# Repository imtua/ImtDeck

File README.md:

# ImtDeck - Your own Cyberdeck

ImtDeck, a cyberdeck designed by **Imtiaz Ahmed**. In ImtDeck, basic tasks and a light AI can be run easily. In this project, it technically contains 2 projects, **ImtDeck-Carrier** and **ImtKeeb-Ortho62**.

**Stardance** project: https://stardance.hackclub.com/projects/54966

# Wanted Ingredients to craft ImtDeck
## Main items-
- **Lattepanda MU + Carrier + Active Cooler** - $250.00 - 1
- **11.6 Inch Screen** - $129.00 - 1
- **Antenna** - $7.99 - 1
- **Audio Card from Waveshare** - $51.71 - 1
- **KAILH Linear Low Profile Switches** - $56.82 - 3
- **Chosfox CFX BoW Keycap Set** - $33.00 - 1
- **TPS43-201A-S** - $13.87 - 1
- **Power Bank** - $13.00 - 1
- **WIFI Card** - $28.00 - 1
- **Pi Pico** - $12.00 - 1
- **USB Micro Cord** - $13.00 - 1
- **40MM Speaker** - $6.00 - 1
- **Tiny SSD** - $70.00 - 1

Check <a href="https://github.com/imtua/ImtDeck/blob/main/ImtDeck%20BOM.csv"><b>ImtDeck BOM.csv</b></a> for links.

## Hardwares-
- 4x M4 Threaded heat-set brass inserts
- 26x M3 Threaded heat-set brass inserts
- 6x M3x8mm Tapered head bolts
- 8x M3x12mm Tapered head bolts
- 4x M3x8mm Socket head bolts
- 4x M3x10mm Socket head bolts
- 2x M4x14mm Socket head bolts
- 2x M4x16mm Socket head bolts
- 2x M4x24mm Socket head bolts
- 1x 7mm OD Carbon fiber rod, 310mm long (can be any material)
- 2x 6.5x2.5mm neodymium magnets (optional)
- 1x Cabinet handle with 4-inch spacing between ends (optional)

# ImtKeeb-Ortho62 - Designed Keyboard for ImtDeck
**ImtKeeb-Ortho62** is a low-profile ortholinear 62 key keyboard that contains a trackpad in it.

**PCB of ImtKeeb-Ortho62:**

**3D PCB of ImtKeeb-Ortho62:**

**ImtKeeb-Ortho62 will feature-**
- <a href="https://www.amazon.com/dp/B0B3MN1ZLW"><b>KAILH Low Profile Switch 1350 Chocolate</b></a> - 62 Switches.
- <a href="https://chosfox.com/collections/keycaps/products/chocfox-bow"><b>Chosfox CFX BoW Keycap Set</b></a> - 62 Keycaps.
- <a href="https://www.digikey.com/en/products/detail/azoteq-pty-ltd/TPS43-201A-S/7164940"><b>TPS43-201A-S</b></a> Trackpad.
- <a href="https://store.roboticsbd.com/raspberry-pi/1599-raspberry-pi-pico-robotics-bangladesh.html"><b>Raspberry Pi Pico</b></a> - Brain of the ImtKeeb-Ortho62.

**Files of ImtKeeb-Ortho62**
- <a href="https://github.com/imtua/ImtDeck/blob/main/production/ImtKeeb-Ortho62/ImtKeeb-Ortho62%20Gerber.zip"><b>ImtKeeb-Ortho62 Gerber Files</a></b> - **/Production/ImtKeeb-Ortho62/ImtKeeb-Ortho62 Gerber.zip**
- <a href="https://github.com/imtua/ImtDeck/blob/main/PCB/ImtKeeb-Ortho62/ImtKeed-Ortho62.kicad_sch"><b>ImtKeeb-Ortho62 Schematics</a><b> - **/PCB/ImtKeeb-Ortho62/ImtKeed-Ortho62.kicad_sch**
- <a href="https://github.com/imtua/ImtDeck/blob/main/PCB/ImtKeeb-Ortho62/ImtKeeb-Ortho62.kicad_pcb"><b>ImtKeeb-Ortho62 PCB</a></b> - **/PCB/ImtKeeb-Ortho62/ImtKeed-Ortho62.kicad_pcb**
- <a href="https://github.com/imtua/ImtDeck/tree/main/QMK"><b>Keyboard QMK config files</b></a> - /QMK

This can be used without the ImtDeck.

# ImtDeck-Carrier - Carrier for MU LattePanda
**ImtDeck-Carrier** is a carrier that holds the lattepanda and makes it route and connect to devices like the monitor, fan, keyboard etc.

**Schematic of ImtDeck-Carrier:**

**PCB of ImtDeck-Carrier:**

**ImtDeck-Carrier** will hold the Lattepanda MU in its place and will distribute powers between items. 

**Files of ImtKeeb-Ortho62**
- <a href="https://github.com/imtua/ImtDeck/blob/main/production/ImtDeck-Carrier/ImtDeck-Carrier%20Gerber.zip"><b>ImtDeck-Carrier Gerber Files</a></b> - **/Production/ImtDeck-Carrier/ImtDeck-Carrier Gerber.zip**
- <a href="https://github.com/imtua/ImtDeck/blob/main/PCB/ImtDeck-Carrier/ImtDeck-Carrier.kicad_sch"><b>ImtDeck-Carrier Schematics</a><b> - **/PCB/ImtDeck-Carrier/ImtDeck-Carrier.kicad_sch**
- <a href="https://github.com/imtua/ImtDeck/blob/main/PCB/ImtDeck-Carrier/ImtDeck-Carrier.kicad_pcbb"><b>ImtDeck-Carrier PCB</a></b> - **/PCB/ImtDeck-Carrier/ImtDeck-Carrier.kicad_pcb**

# Features
- ImtDeck will feature Linux Mint OS in it.
- With it, you can access different tools and a lightweight offline AI in it.
- All ready-to-go device.
- Can play low-end games on it.
- Features Keyboard and Trackpad.
- Sound System.
- Can run everything a normal laptop can.

# Conclusion

Made by <a href="https://github.com/imtua"><b>Imtiaz</b></a> with the help of <a href="https://hackclub.com"><b>Hack Club</a></b>

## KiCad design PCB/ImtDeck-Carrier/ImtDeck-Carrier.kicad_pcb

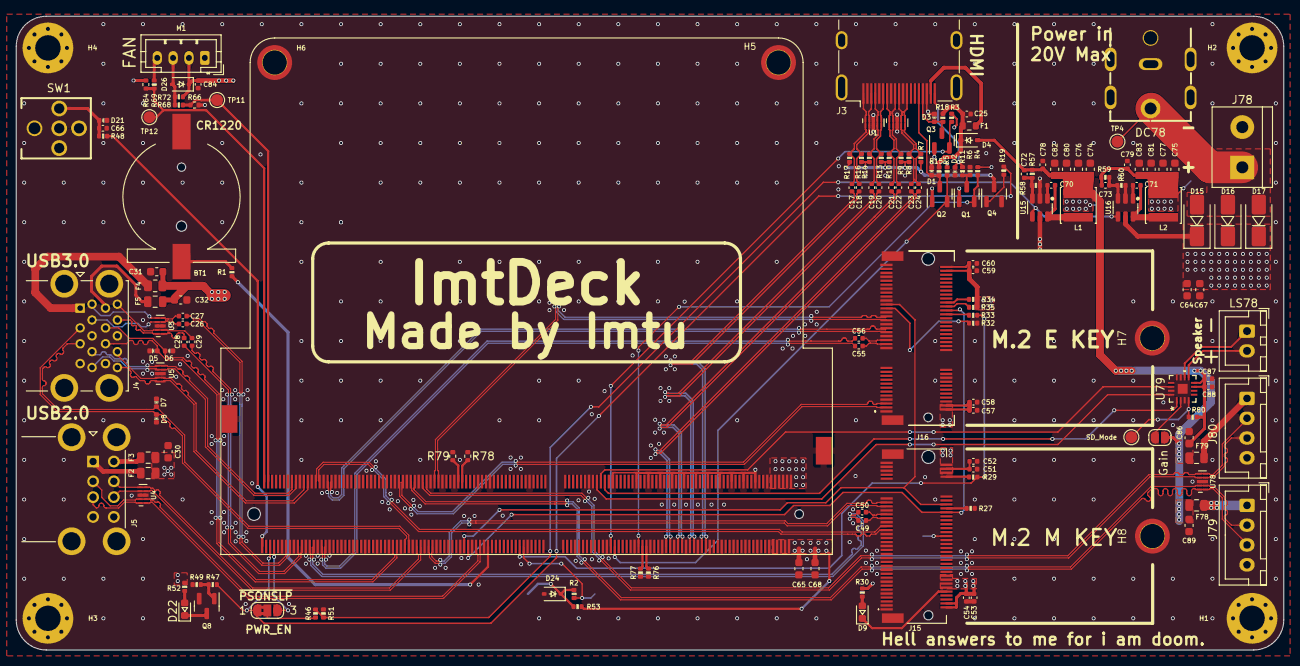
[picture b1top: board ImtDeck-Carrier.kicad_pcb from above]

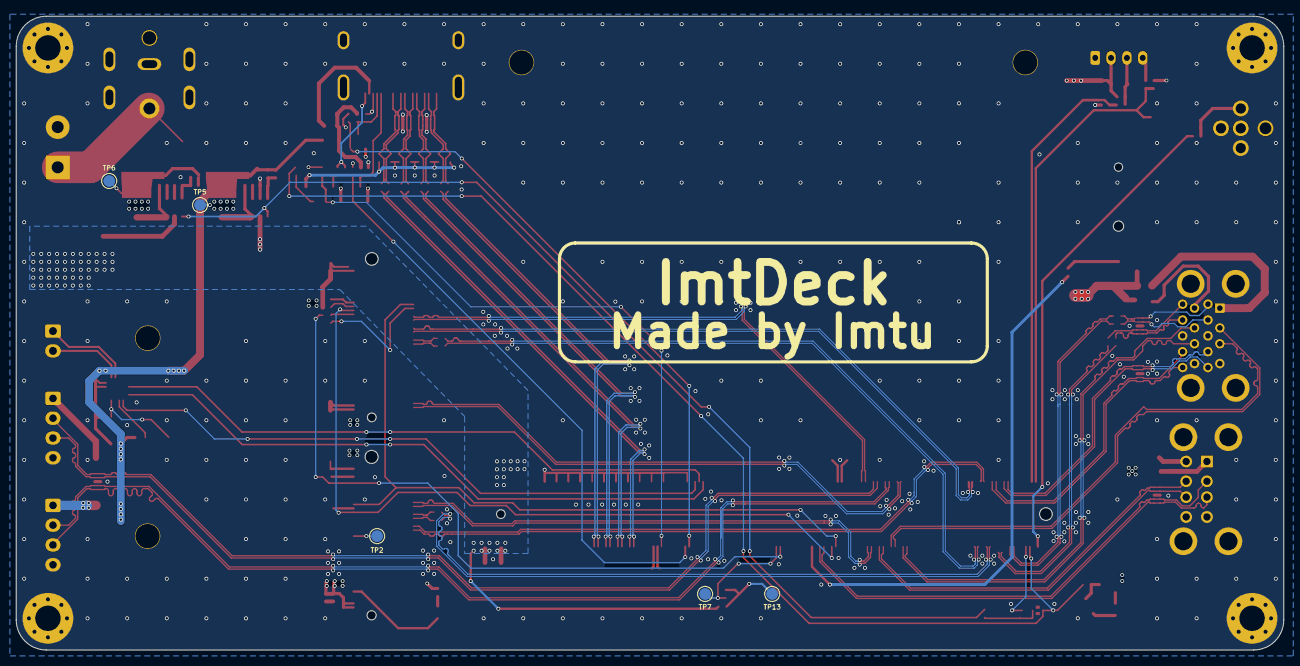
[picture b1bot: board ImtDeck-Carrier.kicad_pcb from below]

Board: 4 copper layers, 160.0 x 80.0 mm, 170 parts (5 on the bottom side), 126 nets.

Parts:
A1: LattePanda_Mu; LattePanda_Module_H8.0mm_Horizontal
BT1: Battery_Cell; Battery_Holder_CR1220_S8411-45R
C17, C18, C19, C20, C21, C22, C23, C24, C25, C26, C27, C28, C29, C52, C54, C58, C60, C70, C71, C78, C79, C84: 100nF/50V; C_0402_1005Metric
C30, C31, C32, C64, C65, C67, C68, C74, C75, C76, C77, C80, C81, C82, C83, C86, C89: 22uF/10V; C_0603_1608Metric
C49, C50, C55, C56: 220nF/50V; C_0402_1005Metric
C51, C53, C57, C59: 10uF/10V; C_0402_1005Metric
C66: 1uF/16V; C_0402_1005Metric
C72, C73: 12pF/50V; C_0402_1005Metric
C87: 10uF; C_0402_1005Metric
C88: 100nF; C_0402_1005Metric
D1, D2, D3, D5, D6, D7, D8, D21: ESD5V0B03; D_0402_1005Metric
D4, D26: 1N5819WS; D_SOD-323
D9, D22: LED_G; LED_0603_1608Metric
D15, D16, D17: SS54; D_SMA
D24: 3V3 Izt=5mA; D_SOD-323
DC78: DC-042C-W-2.0; DC-IN-TH_DC-042C-W-2.0
F1: 6V/50mA; R_0603_1608Metric
F2, F3, F78, F79: 6V/1A; Fuse_0805_2012Metric
F4: 6V/2A; R_0805_2012Metric
F5: 6V/2A; Fuse_0805_2012Metric
Gain: SolderJumper_2_Open; SolderJumper-2_P1.3mm_Open_RoundedPad1.0x1.5mm
H1, H2, H3, H4: MountingHole_Pad; MountingHole_3.2mm_M3_Pad_Via
H5, H6: MountingHole_Pad; MountingHole_3mm_M2_Pad_TopOnly
H7, H8: MountingHole_M2.0; MountingHole_3mm_M2_Pad_TopOnly
J3: HDMI_A; HDMI_A_Molex_208658-1001_Horizontal
J4: USB3_A_Stacked; USB3_A_Molex_48406-0001_Horizontal_Stacked
J5: USB_A_Stacked; USB_A_CUI_UJ2-ADH-TH_Horizontal_Stacked
J15: Bus_M.2_Socket_M; PCIe_M.2_Connectors_P=0.5mm_H=4.2mm_KeyM
J16: Bus_M.2_Socket_E; PCIe_M.2_Connectors_P=0.5mm_H=4.2mm_KeyE
J78: Screw_Terminal_01x02; TerminalBlock_bornier-2_P5.08mm
J79, J80: Conn_01x04_Socket; JST_XH_B4B-XH-A_1x04_P2.50mm_Vertical
JP79: SolderJumper_3_Open; SolderJumper-3_P1.3mm_Bridged2Bar12_RoundedPad1.0x1.5mm_Num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
L1, L2: 2.2uH/4.3A; L_Sunlord_SWPA4020S
LS78: Speaker; JST_XH_B2B-XH-A_1x02_P2.50mm_Vertical
M1: Fan_4pin; JST_PH_B4B-PH-K_1x04_P2.00mm_Vertical
Q1, Q8: 2N7002; SOT-23
Q2, Q3, Q4: 2SK3018; SOT-23
R1, R11, R47: 1K/1%; R_0402_1005Metric
R2, R34, R35, R49, R58, R78, R79: 10K/1%; R_0402_1005Metric
R3, R5, R15, R18, R19, R30, R52, R53: 2.2K/1%; R_0402_1005Metric
R4: 1M/1%; R_0402_1005Metric
R6, R59, R66, R68: 21.5K/1%; R_0402_1005Metric
R7, R8, R9, R10, R13, R14, R16, R17: 470R/1%; R_0402_1005Metric
R27, R29, R32, R33: 0R/1%; R_0402_1005Metric
R46, R48, R69: 100R/1%; R_0402_1005Metric
R51, R76, R77: 100K/1%; R_0402_1005Metric
R57: 75K/1%; R_0402_1005Metric
R60, R64, R72: 4.7K/1%; R_0402_1005Metric
R80: 1M; R_0402_1005Metric
SD_Mode: TestPoint; TestPoint_Pad_D1.5mm
SW1: SW_Push; SW-TH_TM-007-D1-A-03
TP2, TP4, TP5, TP6, TP7, TP11, TP12, TP13: TestPoint; TestPoint_Pad_D1.5mm
U1, U2: TPAZ1023-04F; Diodes_UDFN-10_1.0x2.5mm_P0.5mm
U3, U4, U5, U78: ULC0524P; Diodes_UDFN-10_1.0x2.5mm_P0.5mm
U15, U16: SY8253ADC; TSOT-23-6
U79: MAX98357AETE+T; 21-0136I_T1633-4_MXM

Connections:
5V_HDMI_VCC: C25.1, D4.1 (K), F1.1, R15.1, R18.1
+3V3: C51.2, C52.2, C53.2, C54.2, C57.2, C58.2, C59.2, C60.2, C73.1, C75.2, C77.2, C79.1, C81.2, C83.2, J15.2 (3.3V), J15.4 (3.3V), J15.12 (3.3V), J15.14 (3.3V), J15.16 (3.3V), J15.18 (3.3V), J15.70 (3.3V), J15.72 (3.3V), J15.74 (3.3V), J16.2 (3.3V), J16.4 (3.3V), J16.72 (3.3V), J16.74 (3.3V), L2.2, Q1.1 (G), Q2.1 (G), Q3.1 (G), R3.1, R4.1, R5.1, R30.2, R34.2, R35.1, R52.2, R59.2, R64.1, TP6.1
+5V: C30.2, C31.2, C32.2, C72.1, C74.2, C76.2, C78.1, C80.2, C82.2, C84.1, C86.2, C87.1, C88.1, C89.2, D4.2 (A), D26.1 (K), F2.1, F3.1, F4.1, F5.1, F78.1, F79.1, Gain.1 (A), L1.2, M1.2 (+), R57.2, R72.1, R80.1, TP5.1, U79.7 (VDD), U79.8 (VDD)
+12V: D15.2 (A), D16.2 (A), D17.2 (A), DC78.4, J78.1, TP4.1
+BATT: A1.115 (VBAT), R1.1
/Fan_Temp/FAN_1_PWM: A1.2 (FAN1_PWM), R64.2, R69.1, TP12.1
/Fan_Temp/FAN_1_TAC: A1.4 (FAN1_TAC), R66.1, R68.2, TP11.1
/HDMI/DDC_SCL: D1.2 (A2), J3.15 (SCL), Q2.3 (D), R15.2
/HDMI/DDC_SDA: D3.2 (A2), J3.16 (SDA), Q3.3 (D), R18.2
/HDMI/DDI_B_DDC_SCL: A1.171 (DDIB_DDC_SCL), Q2.2 (S), R5.2
/HDMI/DDI_B_DDC_SDA: A1.169 (DDIB_DDC_SDA), Q3.2 (S), R3.2
/HDMI/DDI_B_HPD: A1.183 (DDIB_HPD), Q1.2 (S), R4.2
/HDMI/DDI_B_TX0+: A1.217 (DDIB_TX0+), C17.1
/HDMI/DDI_B_TX0-: A1.215 (DDIB_TX0-), C18.1
/HDMI/DDI_B_TX1+: A1.211 (DDIB_TX1+), C19.1
/HDMI/DDI_B_TX1-: A1.209 (DDIB_TX1-), C20.1
/HDMI/DDI_B_TX2+: A1.205 (DDIB_TX2+), C21.1
/HDMI/DDI_B_TX2-: A1.203 (DDIB_TX2-), C22.1
/HDMI/DDI_B_TX3+: A1.199 (DDIB_TX3+), C23.1
/HDMI/DDI_B_TX3-: A1.197 (DDIB_TX3-), C24.1
/HDMI/HPD: D2.2 (A2), J3.19 (HPD), R11.2
/HDMI/TMDS_CK+: C23.2, J3.10 (CK+), R8.1, U2.4, U2.7 (NC)
/HDMI/TMDS_CK-: C24.2, J3.12 (CK-), R7.1, U2.5, U2.6 (NC)
/HDMI/TMDS_D0+: C21.2, J3.7 (D0+), R10.1, U2.1, U2.10 (NC)
/HDMI/TMDS_D0-: C22.2, J3.9 (D0-), R9.1, U2.2, U2.9 (NC)
/HDMI/TMDS_D1+: C19.2, J3.4 (D1+), R14.1, U1.4, U1.7 (NC)
/HDMI/TMDS_D1-: C20.2, J3.6 (D1-), R13.1, U1.5, U1.6 (NC)
/HDMI/TMDS_D2+: C17.2, J3.1 (D2+), R17.1, U1.1, U1.10 (NC)
/HDMI/TMDS_D2-: C18.2, J3.3 (D2-), R16.1, U1.2, U1.9 (NC)
/LattePanda Module/HSIO_0_TX+: A1.13 (HSIO0_TX+), C27.1
/LattePanda Module/HSIO_0_TX-: A1.15 (HSIO0_TX-), C26.1
/LattePanda Module/HSIO_1_TX+: A1.19 (HSIO1_TX+), C29.1
/LattePanda Module/HSIO_1_TX-: A1.21 (HSIO1_TX-), C28.1
/LattePanda Module/HSIO_2_RX+: A1.28 (HSIO2_RX+), J15.43 (PERp0/SATA-B-)
/LattePanda Module/HSIO_2_RX-: A1.30 (HSIO2_RX-), J15.41 (PERn0/SATA-B+)
/LattePanda Module/HSIO_2_TX+: A1.25 (HSIO2_TX+), C49.1
/LattePanda Module/HSIO_2_TX-: A1.27 (HSIO2_TX-), C50.1
/LattePanda Module/HSIO_3_RX+: A1.34 (HSIO3_RX+), J16.41 (PERp0)
/LattePanda Module/HSIO_3_RX-: A1.36 (HSIO3_RX-), J16.43 (PERn0)
/LattePanda Module/HSIO_3_TX+: A1.31 (HSIO3_TX+), C55.1
/LattePanda Module/HSIO_3_TX-: A1.33 (HSIO3_TX-), C56.1
/LattePanda Module/REFCLK0+: A1.85 (REFCLK0+), J15.53 (REFCLKn)
/LattePanda Module/REFCLK0-: A1.87 (REFCLK0-), J15.55 (REFCLKp)
/LattePanda Module/REFCLK3+: A1.88 (REFCLK3+), J16.47 (REFCLKp0)
/LattePanda Module/REFCLK3-: A1.90 (REFCLK3-), J16.49 (REFCLKn0)
/LattePanda Module/SLS_S3: A1.7 (SLS_S3), JP79.3 (B)
/LattePanda Module/SUSCLK_WIFI: A1.131 (SUSCLK), R29.2, R33.2
/LattePanda Module/USB_2_P7+: A1.70 (USB2_P4+), J16.3 (USB_D+)
/LattePanda Module/USB_2_P7-: A1.72 (USB2_P4-), J16.5 (USB_D-)
/LattePanda Module/~PWR_SW: A1.1 (~PWRBTN), R48.2
/M.2 E&M Key/CON_PCIE_TX_0+: C55.2, J16.35 (PETp0)
/M.2 E&M Key/CON_PCIE_TX_0-: C56.2, J16.37 (PETn0)
/M.2 E&M Key/CON_PCIE_TX_1+: C49.2, J15.49 (PETp0/SATA-A+)
/M.2 E&M Key/CON_PCIE_TX_1-: C50.2, J15.47 (PETn0/SATA-A-)
/M.2 E&M Key/~CLKREQE: J16.53 (~CLKREQ0), R32.1
/M.2 E&M Key/~CLKREQM: J15.52 (~CLKREQ), R27.1
/PSU/PWR_EN: R46.2, R51.2, U15.4 (EN), U16.4 (EN)
/USB2.0&USB3.0/CON_USB1_D_N: A1.109 (USB2_P5-), J5.2 (D1-), U4.2, U4.9 (NC)
/USB2.0&USB3.0/CON_USB1_D_P: A1.111 (USB2_P5+), J5.3 (D1+), U4.1, U4.10 (NC)
/USB2.0&USB3.0/CON_USB2_D_N: A1.79 (USB2_P3-), J5.6 (D2-), U4.5, U4.6 (NC)
/USB2.0&USB3.0/CON_USB2_D_P: A1.81 (USB2_P3+), J5.7 (D2+), U4.4, U4.7 (NC)
/USB2.0&USB3.0/CON_USB3_D_N: A1.73 (USB2_P2-), D8.2 (A2), J4.2 (D1-)
/USB2.0&USB3.0/CON_USB3_D_P: A1.75 (USB2_P2+), D7.2 (A2), J4.3 (D1+)
/USB2.0&USB3.0/CON_USB3_SSRX_N: A1.18 (HSIO0_RX-), J4.5 (SSRX1-), U5.4, U5.7 (NC)
/USB2.0&USB3.0/CON_USB3_SSRX_P: A1.16 (HSIO0_RX+), J4.6 (SSRX1+), U5.5, U5.6 (NC)
/USB2.0&USB3.0/CON_USB3_SSTX_N: C26.2, J4.8 (SSTX1-), U3.4, U3.7 (NC)
/USB2.0&USB3.0/CON_USB3_SSTX_P: C27.2, J4.9 (SSTX1+), U3.5, U3.6 (NC)
/USB2.0&USB3.0/CON_USB4_D_N: A1.67 (USB2_P1-), D6.2 (A2), J4.11 (D2-)
/USB2.0&USB3.0/CON_USB4_D_P: A1.69 (USB2_P1+), D5.2 (A2), J4.12 (D2+)
/USB2.0&USB3.0/CON_USB4_SSRX_N: A1.24 (HSIO1_RX-), J4.14 (SSRX2-), U5.1, U5.10 (NC)
/USB2.0&USB3.0/CON_USB4_SSRX_P: A1.22 (HSIO1_RX+), J4.15 (SSRX2+), U5.2, U5.9 (NC)
/USB2.0&USB3.0/CON_USB4_SSTX_N: C28.2, J4.17 (SSTX2-), U3.1, U3.10 (NC)
/USB2.0&USB3.0/CON_USB4_SSTX_P: C29.2, J4.18 (SSTX2+), U3.2, U3.9 (NC)
/~PLT_RST: A1.105 (~PLTRST), J15.50 (~PERST), J16.52 (~PERST0)
/~PWR_LED/~PSON: A1.5 (SLS_S0), JP79.1 (A), R19.1, R47.1
/~WAKE: A1.103 (~WAKE), J15.54 (~PEWAKE), J16.55 (~PEWAKE0)
Audio_Data: A1.166 (I2S_TXD), U79.1 (DIN)
BCLK: A1.162 (I2S_SCLK), U79.16 (BCLK)
GND: A1.11 (GND), A1.14 (GND), A1.17 (GND), A1.20 (GND), A1.23 (GND), A1.26 (GND), A1.29 (GND), A1.32 (GND), A1.35 (GND), A1.38 (GND), A1.41 (GND), A1.44 (GND), A1.47 (GND), A1.50 (GND), A1.53 (GND), A1.56 (GND), A1.59 (GND), A1.62 (GND), A1.65 (GND), A1.68 (GND), A1.71 (GND), A1.74 (GND), A1.77 (GND), A1.80 (GND), A1.83 (GND), A1.86 (GND), A1.89 (GND), A1.92 (GND), A1.95 (GND), A1.98 (GND), A1.101 (GND), A1.107 (GND), A1.110 (GND), A1.113 (GND), A1.116 (GND), A1.135 (GND), A1.136 (GND), A1.151 (GND), A1.158 (GND), A1.167 (GND), A1.170 (GND), A1.181 (GND), A1.182 (GND), A1.188 (GND), A1.189 (GND), A1.194 (GND), A1.195 (GND), A1.200 (GND), A1.201 (GND), A1.206 (GND), A1.207 (GND), A1.212 (GND), A1.213 (GND), A1.218 (GND), A1.219 (GND), A1.224 (GND), A1.225 (GND), A1.230 (GND), A1.231 (GND), A1.236 (GND), A1.237 (GND), A1.242 (GND), A1.243 (GND), A1.248 (GND), A1.249 (GND), A1.MP (Mountinge_Pads), BT1.2 (-), C25.2, C30.1, C31.1, C32.1, C51.1, C52.1, C53.1, C54.1, C57.1, C58.1, C59.1, C60.1, C64.1, C65.1, C66.2, C67.1, C68.1, C74.1, C75.1, C76.1, C77.1, C78.2, C79.2, C80.1, C81.1, C82.1, C83.1, C84.2, C86.1, C87.2, C88.2, C89.1, D1.1 (A1), D2.1 (A1), D3.1 (A1), D5.1 (A1), D6.1 (A1), D7.1 (A1), D8.1 (A1), D21.1 (A1), D24.2 (A), DC78.2, DC78.3, H1.1, H2.1, H3.1, H4.1, H5.1, H6.1, H7.1, H8.1, J3.2 (D2S), J3.5 (D1S), J3.8 (D0S), J3.11 (CKS), J3.17 (GND), J3.SH, J4.4 (GND1), J4.7 (DRAIN1), J4.13 (GND2), J4.16 (DRAIN2), J4.19 (SHIELD), J5.4 (GND1), J5.8 (GND2), J5.9 (Shield), J15.1 (GND), J15.3 (GND), J15.9 (GND), J15.15 (GND), J15.21 (GND), J15.27 (GND), J15.33 (GND), J15.39 (GND), J15.45 (GND), J15.51 (GND), J15.57 (GND), J15.71 (GND), J15.73 (GND), J15.75 (GND), J15.MP1, J15.MP2, J16.1 (GND), J16.7 (GND), J16.18 (GND), J16.33 (GND), J16.39 (GND), J16.45 (GND), J16.51 (GND), J16.57 (GND), J16.63 (GND), J16.69 (GND), J16.75 (GND), J16.MP1, J16.MP2, J78.2, J79.4, J80.4, M1.1 (-), Q4.2 (S), Q8.2 (S), R6.2, R27.2, R32.2, R49.1, R51.1, R58.1, R60.1, R66.2, R76.2, R77.2, R78.2, R79.2, SW1.2, U1.3 (VSS), U1.8 (VSS), U2.3 (VSS), U2.8 (VSS), U3.3 (VSS), U3.8 (VSS), U4.3 (VSS), U4.8 (VSS), U5.3 (VSS), U5.8 (VSS), U15.2 (GND), U16.2 (GND), U78.3 (VSS), U78.8 (VSS), U79.3 (GND), U79.11 (GND), U79.15 (GND), U79.17 (EPAD)
LRCLK: A1.164 (I2S_SFRM), U79.14 (LRCLK)
unnamed: A1.187 (TCP0_HPD), R76.1
unnamed: A1.185 (TCP1_HPD), R77.1
unnamed: A1.133 (~BIOS_SEL), R2.1, TP7.1
unnamed: A1.100 (~CLKREQ3), R79.1
unnamed: A1.102 (~CLKREQ4), R78.1
unnamed: BT1.1 (+), R1.2
unnamed: D9.2 (A), R30.1
unnamed: D9.1 (K), J15.10 (DAS/~DSS/~LED1)
unnamed: D22.2 (A), R52.1
unnamed: D22.1 (K), Q8.3 (D)
unnamed: D26.2 (A), M1.3 (Tacho), R68.1, R72.2
unnamed: F1.2, J3.18 (+5V)
unnamed: F4.2, J4.1 (VBUS1)
unnamed: F5.2, J4.10 (VBUS2)
unnamed: F2.2, J5.1 (VBUS1)
unnamed: F3.2, J5.5 (VBUS2)
unnamed: J15.38 (DEVSLP), TP2.1
unnamed: J15.68 (SUSCLK), R29.1
unnamed: J16.50 (SUSCLK), R33.1
unnamed: J16.56 (~W_DISABLE1), R34.1
unnamed: J16.54 (~W_DISABLE2), R35.2
unnamed: F78.2, J79.1
unnamed: F79.2, J80.1
unnamed: Gain.2 (B), U79.2 (GAIN_SLOT)
unnamed: JP79.2 (C), R46.1
unnamed: M1.4 (PWM), R69.2
unnamed: Q1.3 (D), R6.1, R11.1
unnamed: Q4.3 (D), R7.2, R8.2, R9.2, R10.2, R13.2, R14.2, R16.2, R17.2
unnamed: Q4.1 (G), R19.2
unnamed: Q8.1 (G), R47.2, R49.2
unnamed: C70.2, U15.1 (BOOST)
unnamed: C72.2, R57.1, R58.2, U15.3 (FB)
unnamed: C70.1, L1.1, U15.6 (SW)
unnamed: C71.2, U16.1 (BOOST)
unnamed: C73.2, R59.1, R60.2, U16.3 (FB)
unnamed: C71.1, L2.1, U16.6 (SW)
unnamed: R80.2, SD_Mode.1, U79.4 (*SD_MODE)
unnamed: LS78.1, U79.10 (OUTN)
unnamed: LS78.2, U79.9 (OUTP)
PWR: C66.1, D21.2 (A2), R48.1, SW1.1
USB_2_FP1+: A1.76 (USB2_P7+), J79.3, U78.1, U78.10 (NC)
USB_2_FP1-: A1.78 (USB2_P7-), J79.2, U78.2, U78.9 (NC)
USB_2_FP2+: A1.82 (USB2_P8+), J80.3, U78.4, U78.7 (NC)
USB_2_FP2-: A1.84 (USB2_P8-), J80.2, U78.5, U78.6 (NC)
VDC: A1.250 (VIN), A1.251 (VIN), A1.252 (VIN), A1.253 (VIN), A1.254 (VIN), A1.255 (VIN), A1.256 (VIN), A1.257 (VIN), A1.258 (VIN), A1.259 (VIN), A1.260 (VIN), C64.2, C65.2, C67.2, C68.2, D15.1 (K), D16.1 (K), D17.1 (K), R53.1, U15.5 (VIN), U16.5 (VIN)
VPullup: D24.1 (K), R2.2, R53.2, TP13.1

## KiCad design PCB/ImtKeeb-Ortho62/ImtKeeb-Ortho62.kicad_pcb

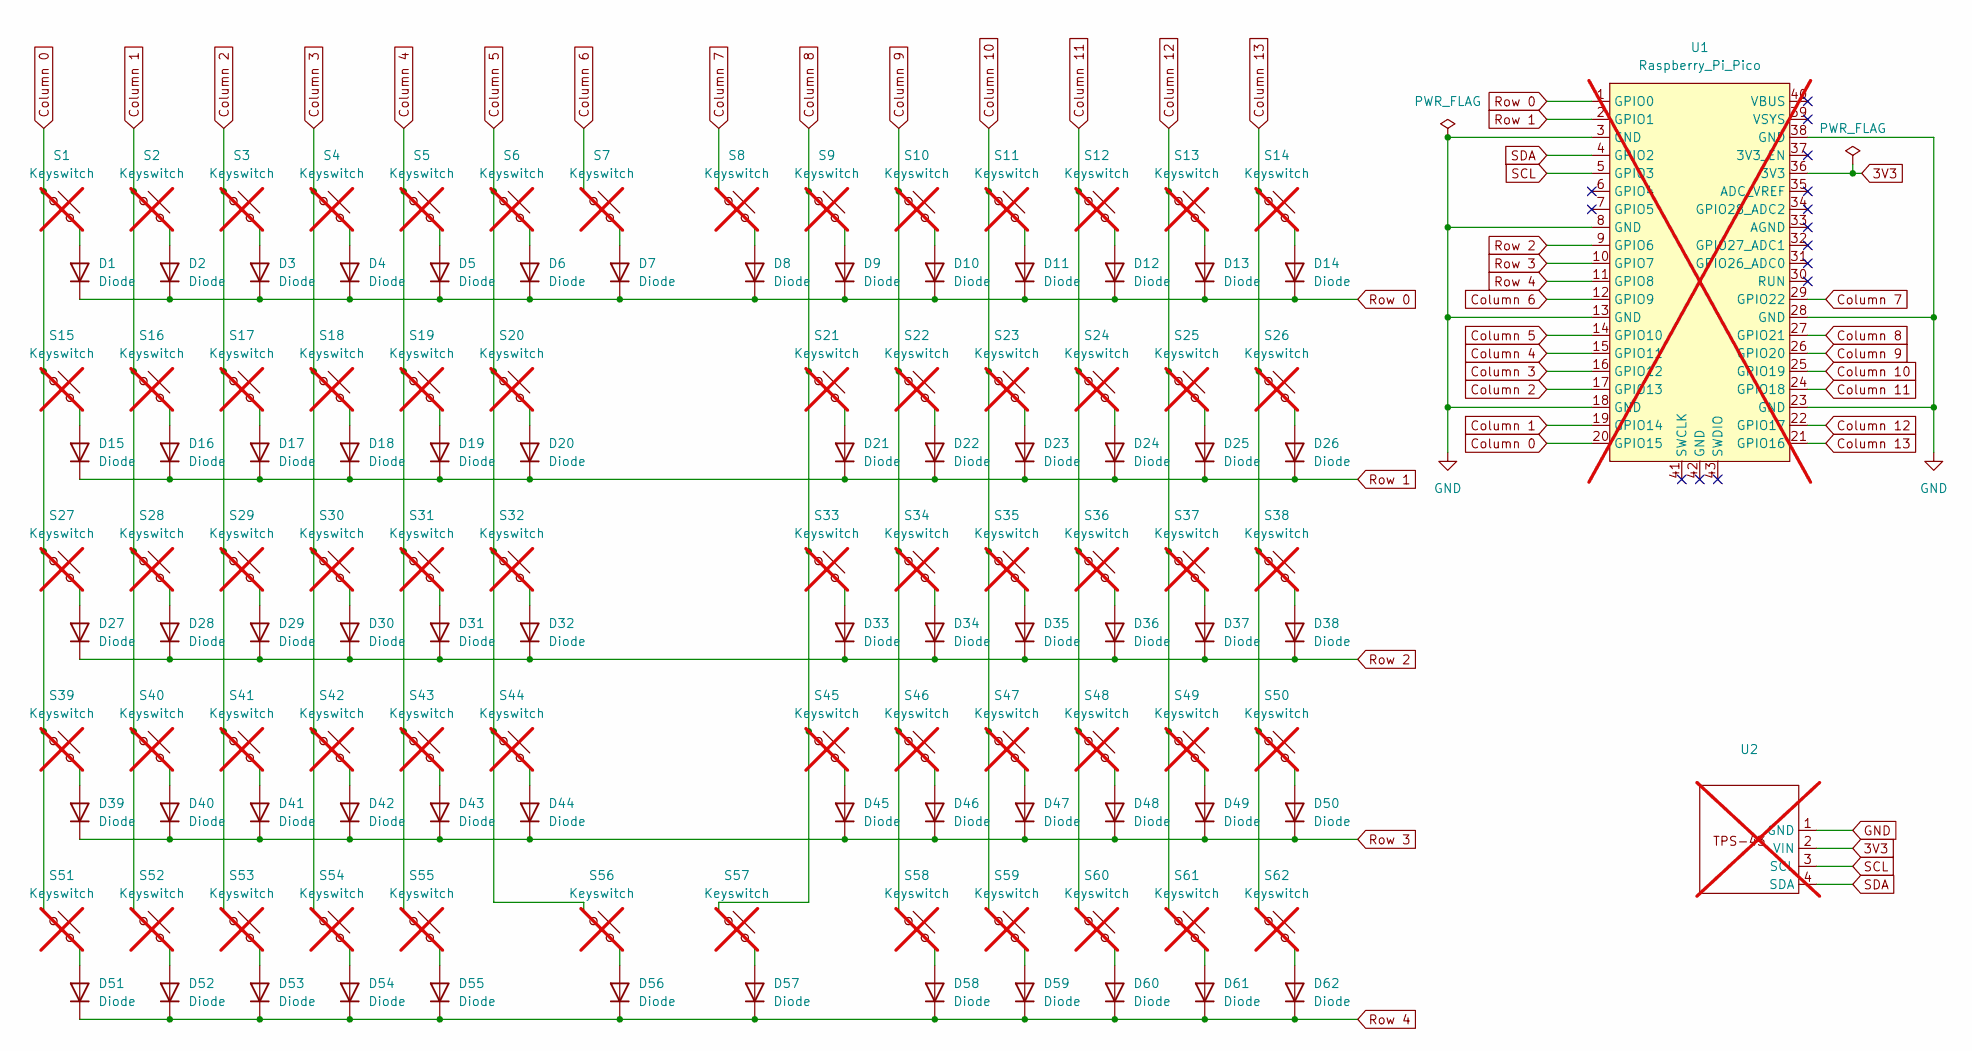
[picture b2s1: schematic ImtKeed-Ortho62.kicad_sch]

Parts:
D1, D2, D3, D4, D5, D6, D7, D8, D9, D10, D11, D12, D13, D14, D15, D16, D17, D18, D19, D20, D21, D22, D23, D24, D25, D26, D27, D28, D29, D30, D31, D32, D33, D34, D35, D36, D37, D38, D39, D40, D41, D42, D43, D44, D45, D46, D47, D48, D49, D50, D51, D52, D53, D54, D55, D56, D57, D58, D59, D60, D61, D62: Diode; Diode_SOD-123; MPN 1N4148W-7-F
S1, S2, S3, S4, S5, S6, S7, S8, S9, S10, S11, S12, S13, S14, S15, S16, S17, S18, S19, S20, S21, S22, S23, S24, S25, S26, S27, S28, S29, S30, S31, S32, S33, S34, S35, S36, S37, S38, S39, S40, S41, S42, S43, S44, S45, S46, S47, S48, S49, S50, S51, S52, S53, S54, S56, S57, S59, S60, S61, S62: Keyswitch; Choc_V1; not fitted
S55, S58: Keyswitch; Choc_V1_2.00u; not fitted
U1: Raspberry_Pi_Pico; not fitted
U2: PinHeader_1x04_P2.54mm_Vertical; not fitted

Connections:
3V3: U1.36 (3V3), U2.2 (VIN)
Column 0: S1.1, S15.1, S27.1, S39.1, S51.1, U1.20 (GPIO15)
Column 1: S2.1, S16.1, S28.1, S40.1, S52.1, U1.19 (GPIO14)
Column 2: S3.1, S17.1, S29.1, S41.1, S53.1, U1.17 (GPIO13)
Column 3: S4.1, S18.1, S30.1, S42.1, S54.1, U1.16 (GPIO12)
Column 4: S5.1, S19.1, S31.1, S43.1, S55.1, U1.15 (GPIO11)
Column 5: S6.1, S20.1, S32.1, S44.1, S56.1, U1.14 (GPIO10)
Column 6: S7.1, U1.12 (GPIO9)
Column 7: S8.1, U1.29 (GPIO22)
Column 8: S9.1, S21.1, S33.1, S45.1, S57.1, U1.27 (GPIO21)
Column 9: S10.1, S22.1, S34.1, S46.1, S58.1, U1.26 (GPIO20)
Column 10: S11.1, S23.1, S35.1, S47.1, S59.1, U1.25 (GPIO19)
Column 11: S12.1, S24.1, S36.1, S48.1, S60.1, U1.24 (GPIO18)
Column 12: S13.1, S25.1, S37.1, S49.1, S61.1, U1.22 (GPIO17)
Column 13: S14.1, S26.1, S38.1, S50.1, S62.1, U1.21 (GPIO16)
GND: U1.3 (GND), U1.8 (GND), U1.13 (GND), U1.18 (GND), U1.23 (GND), U1.28 (GND), U1.38 (GND), U2.1 (GND)
unnamed: D1.2 (A), S1.2
unnamed: D2.2 (A), S2.2
unnamed: D3.2 (A), S3.2
unnamed: D4.2 (A), S4.2
unnamed: D5.2 (A), S5.2
unnamed: D6.2 (A), S6.2
unnamed: D7.2 (A), S7.2
unnamed: D8.2 (A), S8.2
unnamed: D9.2 (A), S9.2
unnamed: D10.2 (A), S10.2
unnamed: D11.2 (A), S11.2
unnamed: D12.2 (A), S12.2
unnamed: D13.2 (A), S13.2
unnamed: D14.2 (A), S14.2
unnamed: D15.2 (A), S15.2
unnamed: D16.2 (A), S16.2
unnamed: D17.2 (A), S17.2
unnamed: D18.2 (A), S18.2
unnamed: D19.2 (A), S19.2
unnamed: D20.2 (A), S20.2
unnamed: D21.2 (A), S21.2
unnamed: D22.2 (A), S22.2
unnamed: D23.2 (A), S23.2
unnamed: D24.2 (A), S24.2
unnamed: D25.2 (A), S25.2
unnamed: D26.2 (A), S26.2
unnamed: D27.2 (A), S27.2
unnamed: D28.2 (A), S28.2
unnamed: D29.2 (A), S29.2
unnamed: D30.2 (A), S30.2
unnamed: D31.2 (A), S31.2
unnamed: D32.2 (A), S32.2
unnamed: D33.2 (A), S33.2
unnamed: D34.2 (A), S34.2
unnamed: D35.2 (A), S35.2
unnamed: D36.2 (A), S36.2
unnamed: D37.2 (A), S37.2
unnamed: D38.2 (A), S38.2
unnamed: D39.2 (A), S39.2
unnamed: D40.2 (A), S40.2
unnamed: D41.2 (A), S41.2
unnamed: D42.2 (A), S42.2
unnamed: D43.2 (A), S43.2
unnamed: D44.2 (A), S44.2
unnamed: D45.2 (A), S45.2
unnamed: D46.2 (A), S46.2
unnamed: D47.2 (A), S47.2
unnamed: D48.2 (A), S48.2
unnamed: D49.2 (A), S49.2
unnamed: D50.2 (A), S50.2
unnamed: D51.2 (A), S51.2
unnamed: D52.2 (A), S52.2
unnamed: D53.2 (A), S53.2
unnamed: D54.2 (A), S54.2
unnamed: D55.2 (A), S55.2
unnamed: D56.2 (A), S56.2
unnamed: D57.2 (A), S57.2
unnamed: D58.2 (A), S58.2
unnamed: D59.2 (A), S59.2
unnamed: D60.2 (A), S60.2
unnamed: D61.2 (A), S61.2
unnamed: D62.2 (A), S62.2
Row 0: D1.1 (K), D2.1 (K), D3.1 (K), D4.1 (K), D5.1 (K), D6.1 (K), D7.1 (K), D8.1 (K), D9.1 (K), D10.1 (K), D11.1 (K), D12.1 (K), D13.1 (K), D14.1 (K), U1.1 (GPIO0)
Row 1: D15.1 (K), D16.1 (K), D17.1 (K), D18.1 (K), D19.1 (K), D20.1 (K), D21.1 (K), D22.1 (K), D23.1 (K), D24.1 (K), D25.1 (K), D26.1 (K), U1.2 (GPIO1)
Row 2: D27.1 (K), D28.1 (K), D29.1 (K), D30.1 (K), D31.1 (K), D32.1 (K), D33.1 (K), D34.1 (K), D35.1 (K), D36.1 (K), D37.1 (K), D38.1 (K), U1.9 (GPIO6)
Row 3: D39.1 (K), D40.1 (K), D41.1 (K), D42.1 (K), D43.1 (K), D44.1 (K), D45.1 (K), D46.1 (K), D47.1 (K), D48.1 (K), D49.1 (K), D50.1 (K), U1.10 (GPIO7)
Row 4: D51.1 (K), D52.1 (K), D53.1 (K), D54.1 (K), D55.1 (K), D56.1 (K), D57.1 (K), D58.1 (K), D59.1 (K), D60.1 (K), D61.1 (K), D62.1 (K), U1.11 (GPIO8)
SCL: U1.5 (GPIO3), U2.3 (SCL)
SDA: U1.4 (GPIO2), U2.4 (SDA)

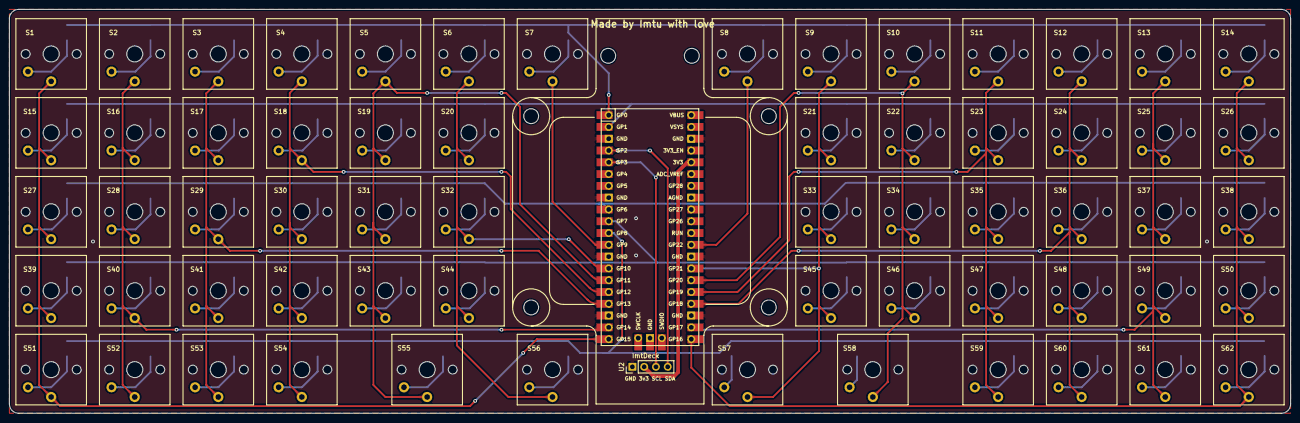
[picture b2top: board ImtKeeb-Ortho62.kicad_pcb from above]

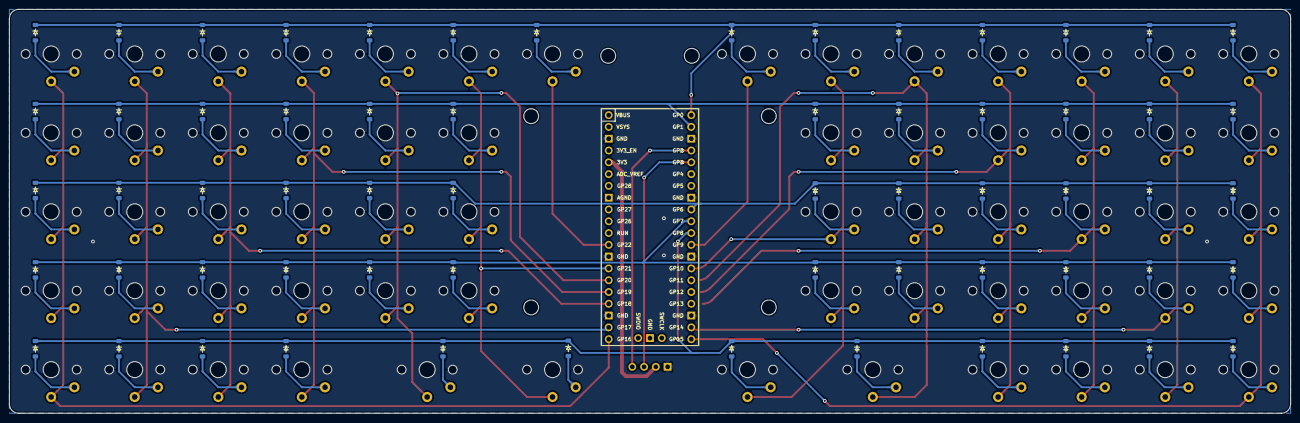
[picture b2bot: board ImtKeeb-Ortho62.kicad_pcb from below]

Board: 2 copper layers, 276.0 x 87.0 mm, 126 parts (62 on the bottom side), 85 nets.
